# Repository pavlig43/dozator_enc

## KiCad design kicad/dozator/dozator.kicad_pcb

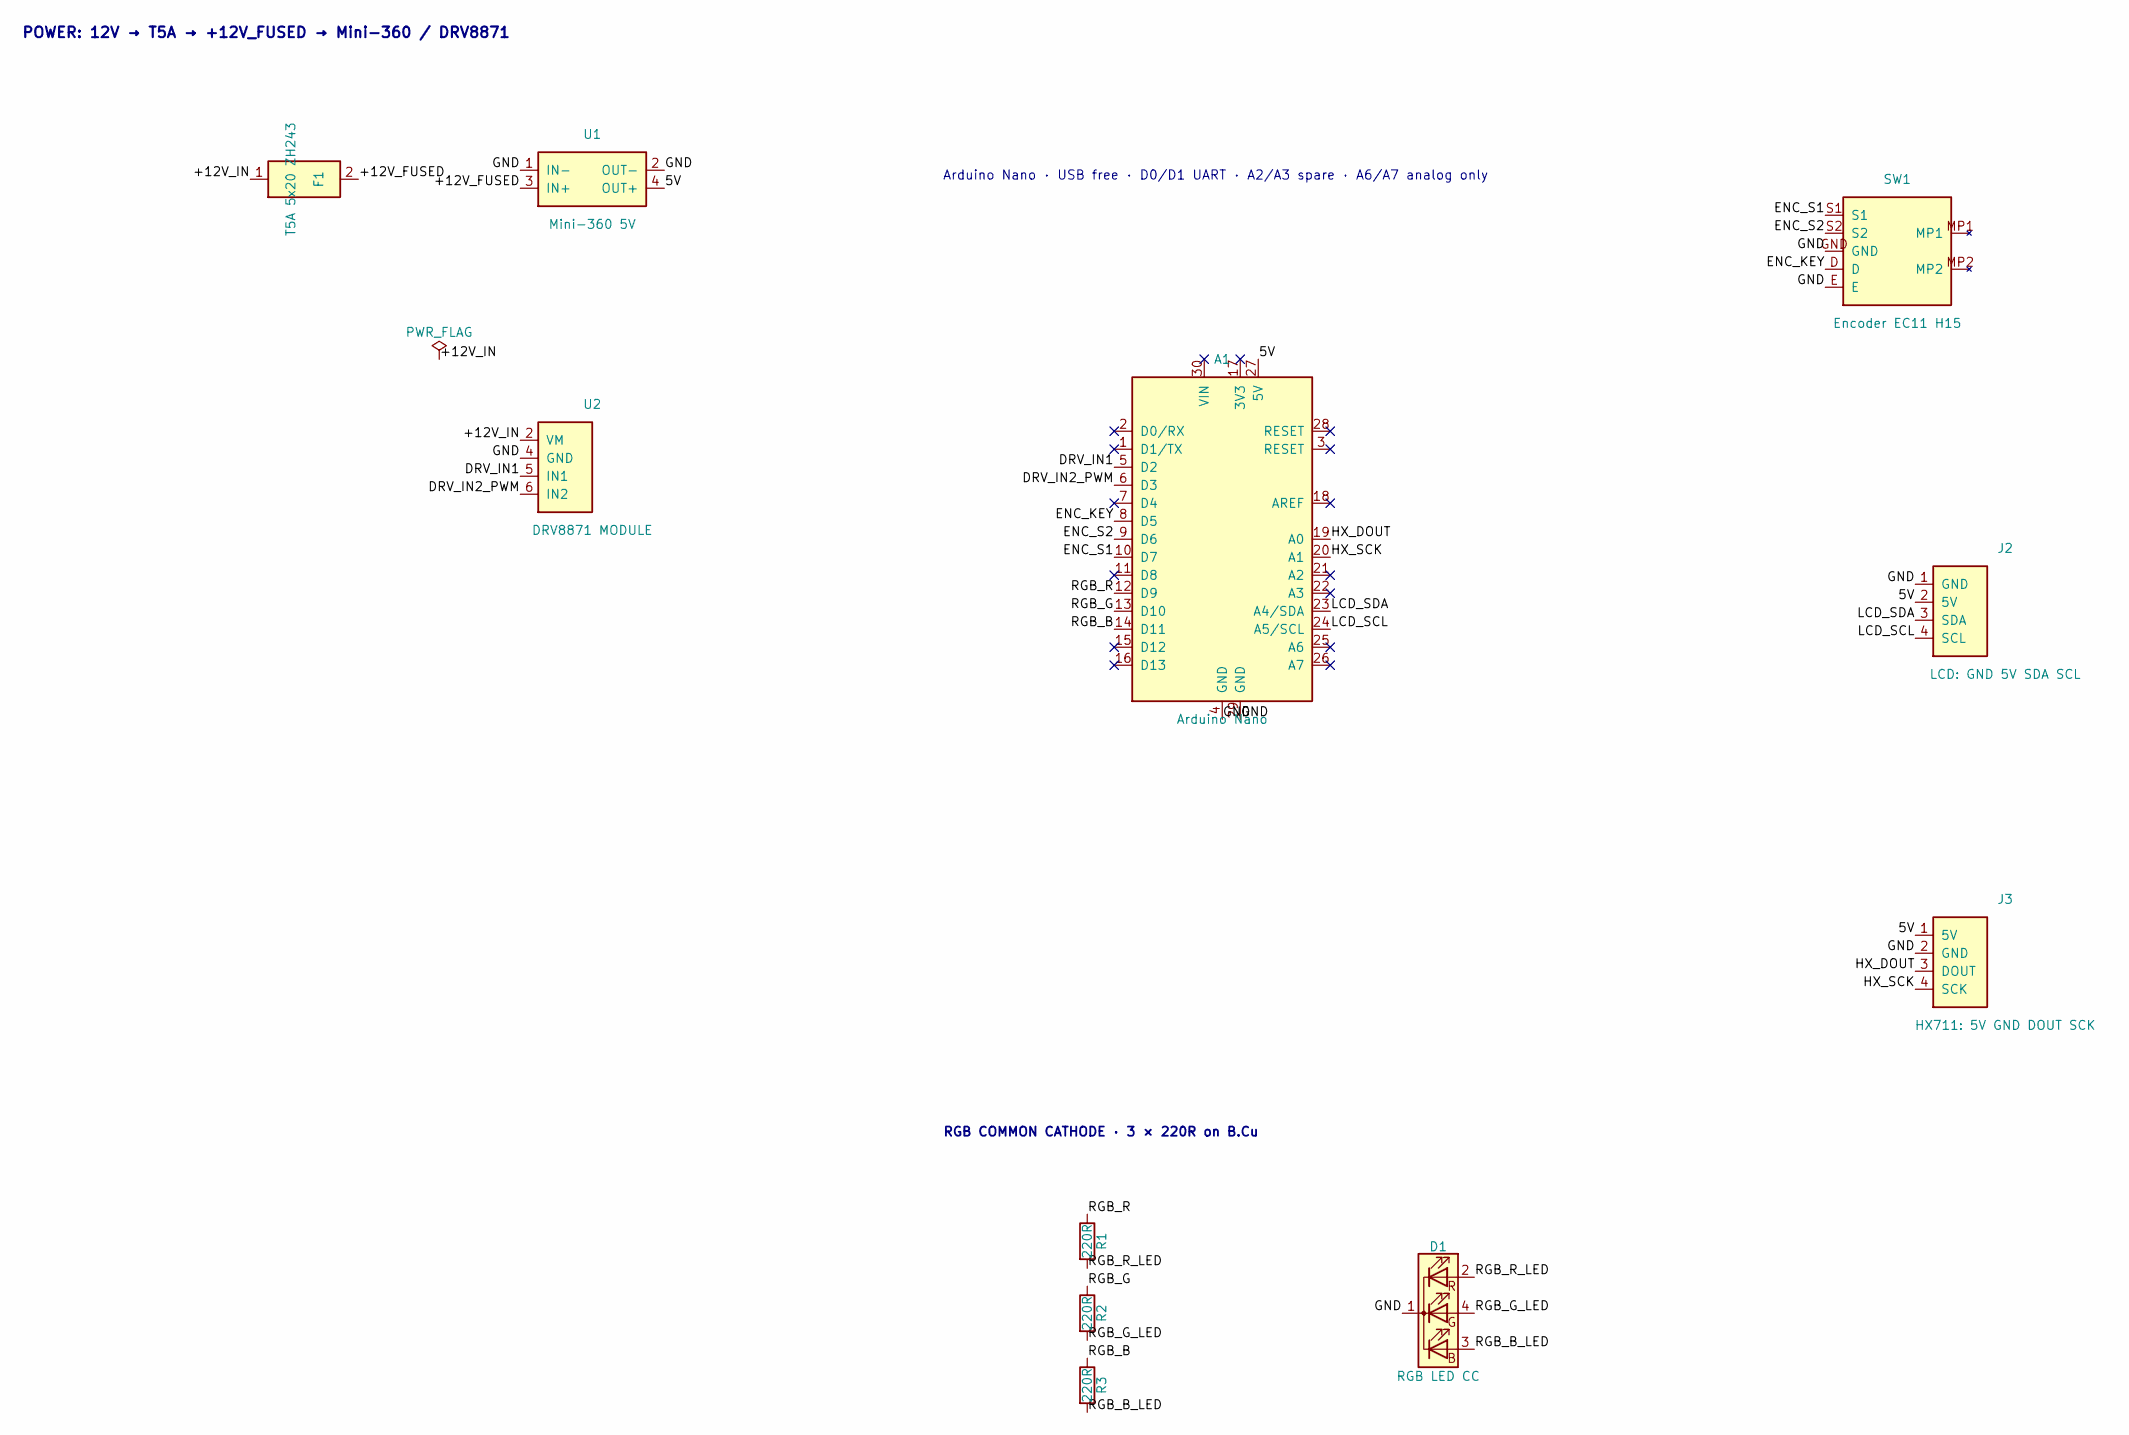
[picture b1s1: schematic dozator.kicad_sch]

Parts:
A1: Arduino Nano; Arduino_Nano
D1: RGB LED CC; LED_D5.0mm-4_RGB
F1: T5A 5x20 ZH243; Fuseholder_ZH243_5x20_P22mm
J2: LCD: GND 5V SDA SCL; PinHeader_1x04_P2.54mm_Horizontal
J3: HX711: 5V GND DOUT SCK; PinHeader_1x04_P2.54mm_Horizontal
R1, R2, R3: 220R; R_1206_3216Metric
SW1: Encoder EC11 H15; RotaryEncoder_EC11_Switch_Vertical_H15mm
U1: Mini-360 5V; DC_DC_MINI360
U2: DRV8871 MODULE; DRV8871_Module

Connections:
/5V: A1.27 (5V), J2.2 (5V), J3.1 (5V), U1.4 (OUT+)
/+12V_FUSED: F1.2 (FUSED), U1.3 (IN+)
/+12V_IN: F1.1 (IN), U2.2 (VM)
/DRV_IN1: A1.5 (D2), U2.5 (IN1)
/DRV_IN2_PWM: A1.6 (D3), U2.6 (IN2)
/ENC_KEY: A1.8 (D5), SW1.D
/ENC_S1: A1.10 (D7), SW1.S1
/ENC_S2: A1.9 (D6), SW1.S2
/GND: A1.4 (GND), A1.29 (GND), D1.1 (K), J2.1 (GND), J3.2 (GND), SW1.E, SW1.GND, U1.1 (IN-), U1.2 (OUT-), U2.4 (GND)
/HX_DOUT: A1.19 (A0), J3.3 (DOUT)
/HX_SCK: A1.20 (A1), J3.4 (SCK)
/LCD_SCL: A1.24 (A5/SCL), J2.4 (SCL)
/LCD_SDA: A1.23 (A4/SDA), J2.3 (SDA)
/RGB_B: A1.14 (D11), R3.1
/RGB_B_LED: D1.3 (BA), R3.2
/RGB_G: A1.13 (D10), R2.1
/RGB_G_LED: D1.4 (GA), R2.2
/RGB_R: A1.12 (D9), R1.1
/RGB_R_LED: D1.2 (RA), R1.2

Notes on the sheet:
POWER: 12V → T5A → +12V_FUSED → Mini-360 / DRV8871
Arduino Nano · USB free · D0/D1 UART · A2/A3 spare · A6/A7 analog only
RGB COMMON CATHODE · 3 × 220R on B.Cu

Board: 2 copper layers, 11 parts (6 on the bottom side), 19 nets, no tracks yet.
